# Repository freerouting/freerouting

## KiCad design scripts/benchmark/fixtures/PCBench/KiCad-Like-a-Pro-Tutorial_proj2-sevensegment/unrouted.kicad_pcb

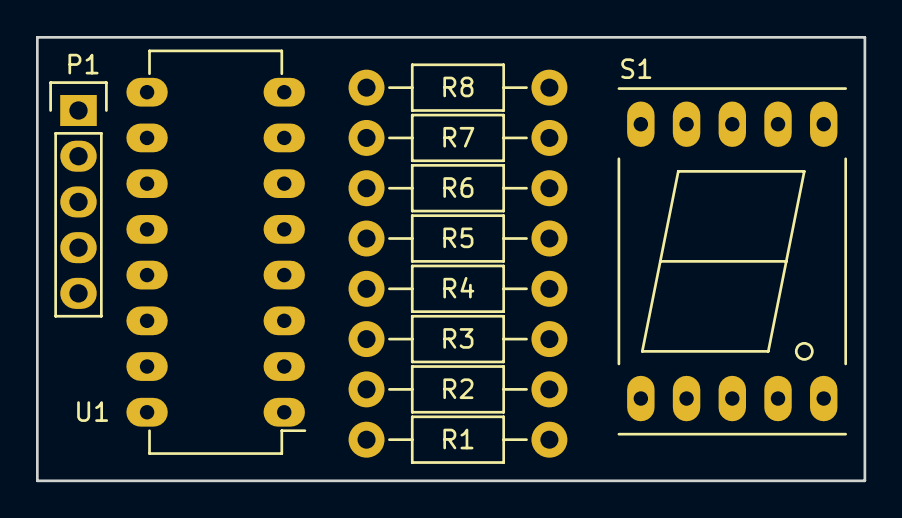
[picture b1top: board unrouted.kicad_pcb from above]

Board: 2 copper layers, 46.0 x 24.6 mm, 11 parts (0 on the bottom side), 21 nets, no tracks yet.

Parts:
P1: CONN_01X05; Pin_Header_Straight_1x05
R1, R2, R3, R4, R5, R6, R7, R8: 220; Resistor_Horizontal_RM10mm
S1: 7SEGM; 7SegmentLED_LTS6760_LTS6780
U1: 74HC595; DIP-16_W7.62mm_LongPads

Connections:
/A: R1.1, S1.7
/B: R2.1, S1.6
/C: R3.1, S1.4
/CLOCK: P1.4, U1.12
/D: R4.1, S1.2
/DATA: P1.3, U1.11
/E: R5.1, S1.1
/F: R6.1, S1.9
/G: R7.1, S1.10
/H: R8.1, S1.5
/LATCH: P1.2, U1.14
/QA: R1.2, U1.15
/QB: R2.2, U1.1
/QC: R3.2, U1.2
/QD: R4.2, U1.3
/QE: R5.2, U1.4
/QF: R6.2, U1.5
/QG: R7.2, U1.6
/QH: R8.2, U1.7
GND: P1.5, U1.8, U1.13
VCC: P1.1, S1.3, S1.8, U1.10, U1.16

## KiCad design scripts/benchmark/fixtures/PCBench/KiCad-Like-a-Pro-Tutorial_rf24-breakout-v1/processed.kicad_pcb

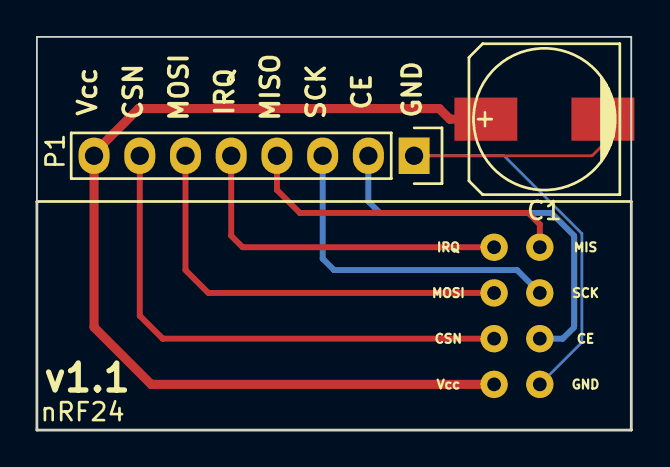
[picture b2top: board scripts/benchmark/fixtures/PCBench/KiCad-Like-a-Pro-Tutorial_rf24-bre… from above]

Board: 2 copper layers, 33.0 x 21.8 mm, 3 parts (0 on the bottom side), 8 nets.

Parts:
C1: 1uF; c_elec_8x10.5
P1: CONN_01X08; Pin_Header_Straight_1x08
U1: nRF24

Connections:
/CE: P1.2, U1.1
/CSN: P1.7, U1.6
/IRQ: P1.5, U1.4
/MIS: P1.4, U1.3
/MOSI: P1.6, U1.5
/SCK: P1.3, U1.2
/Vcc: C1.1, P1.8, U1.7
GND: C1.2, P1.1, U1.0

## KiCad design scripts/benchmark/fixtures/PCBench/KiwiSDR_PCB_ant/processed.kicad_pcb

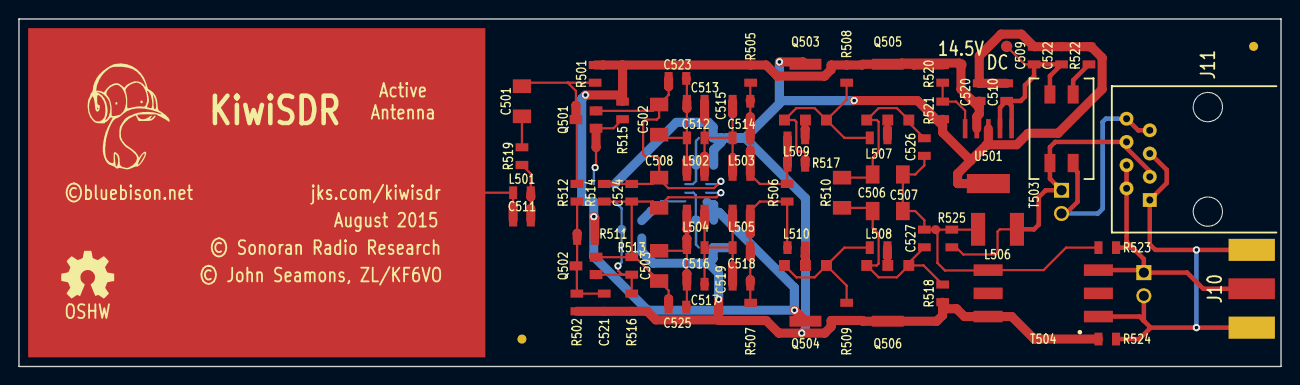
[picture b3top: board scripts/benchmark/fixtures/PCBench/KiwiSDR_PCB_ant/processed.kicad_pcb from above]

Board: 2 copper layers, 138.0 x 38.0 mm, 85 parts (0 on the bottom side), 36 nets.

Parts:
C501, C502, C503, C506, C507, C508: 470n/100; kiwi-SM1206
C504, C505: DNL 470n/100; kiwi-SM1206
C509: 100n/100; kiwi-SM0805
C510, C520: 10u/25; kiwi-SM0805
C511, C512, C513, C514, C515, C516, C517, C518, C519: DNL; kiwi-SM0805
C521: DNL 100n/100; kiwi-SM0805
C522, C523, C524, C525, C526, C527: 1n/100; kiwi-SM0805
EP501: E_FIELD_PROBE; kiwi-E_FIELD_PROBE
FID1, FID2: FIDUCIAL; kiwi-FIDUCIAL_2_SIDE
GFX1: LOGO; kiwi-KIWI_10MM
GFX3: OSHW; kiwi-OSHW_6MM
J10: DNL BNC; kiwi-BNC_SMA_NO_VIP
J11: DNL RJ45; kiwi-RJ45_8
J12: DNL TB_2; kiwi-TB_2P_2_54MM
J13: TB_2; kiwi-TB_2P_2_54MM
L501, L502, L503, L504, L505: 0R; kiwi-SM0805
L506: 100uH; kiwi-SM1812
L507, L508, L509, L510: FB 80Z; kiwi-SM0805
Q501: J310; kiwi-SOT23_DGS
Q502: J271; kiwi-SOT23_DGS
Q503, Q506: BFG31; kiwi-SOT223_EBEC
Q504, Q505: BFG35; kiwi-SOT223_EBEC
Q507: DNL J310; kiwi-SOT23_DGS
R501, R502: 1M; kiwi-SM0805
R503, R504: DNL 100R; kiwi-SM0805
R505, R507: 100K; kiwi-SM0805
R506: 2K2; kiwi-SM0805
R508, R509: 470R; kiwi-SM0805
R510: 10R/0.66W; kiwi-SM1206
R511: DNL 1M; kiwi-SM0805
R512, R515, R516, R519, R523, R524: 0R; kiwi-SM0805
R513, R518: DNL 0R; kiwi-SM0805
R514: 100R; kiwi-SM0805
R517: DNL 47R; kiwi-SM0805
R520: 11K; kiwi-SM0805
R521: 1K; kiwi-SM0805
R522: DNL; kiwi-SM0805
R525: 1K5; kiwi-SM0805
T501: DNL T-622; kiwi-MCL_KK81
T502, T504: DNL T1-6; kiwi-MCL_KK81
T503: CMC 2 mH; kiwi-CMC
TP501, TP502: TEST_POINT; kiwi-TP_1250
U501: TPS7A4501; kiwi-SOT223_6

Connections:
/14.55: C520.1, Q504.C, Q505.C, R501.1, R503.1, R505.1, R508.1, R511.1, R515.1, R520.1, T501.3, T502.4, TP502.1, U501.4
/ANT2: C511.2, L501.1, R519.1
/ANT3: C501.1, R519.2
/ANT4: C501.2, Q501.G, R501.2, R512.1
/B1H: L509.2, Q503.B
/B1L: L510.2, Q504.B
/B2H: L507.2, Q505.B
/B2L: L508.2, Q506.B
/BIAS: C521.1, Q502.G, R502.2, R511.2, R512.2
/BIAS+: J11.3, J11.6, J12.1, L506.2, R525.1, T503.3
/BIAS-: J11.7, J11.8, J12.2, T503.4
/DCIN: C509.1, C510.1, C522.1, T503.2, TP501.1, U501.1, U501.2
/E1H: L507.1, Q503.E1, Q503.E2, R508.2, R517.1
/E1L: L508.1, Q504.E1, Q504.E2, R509.1
/E2H: C506.1, C526.1, Q505.E1, Q505.E2, R510.1
/E2L: C507.1, C527.1, Q506.E1, Q506.E2, R510.2, R518.1
/EPROBE: C511.1, EP501.1, L501.2
/FB1: Q501.D, R515.2, T502.6
/FB2: Q502.D, Q507.G, R513.1, R516.2, T502.3
/FB3: Q507.D, T501.4
/JHI: C502.1, C508.1, C523.1, C524.1, Q501.S, R514.2, T501.1
/JLO: C503.1, C508.2, C524.2, C525.1, Q502.S, R513.2, R514.1, T501.2
/NF1H: C502.2, C512.1, C513.1, C523.2, L502.1
/NF1L: C503.2, C516.1, C517.1, C525.2, L504.1
/NF2H: C512.2, C513.2, C514.1, C515.1, L502.2, L503.1
/NF2L: C516.2, C517.2, C518.1, C519.1, L504.2, L505.1
/NF3H: C514.2, C515.2, L503.2, L509.1, R505.2, R506.1, R517.2
/NF3L: C518.2, C519.2, L505.2, L510.1, R506.2, R507.1
/OUT: C506.2, C507.2, C526.2, C527.2, L506.1, R523.2, R525.2, T504.3
/RX+: J10.1, J11.2, J11.4, J13.1, R523.1, T504.4
/RX-: J10.2, J10.3, J11.1, J11.5, J13.2, R524.1, T504.6
/THI: C505.1, R504.2, T501.6
/TLO: C504.2, R503.2, T501.5
/TP: R522.1, T503.1
/VADJ: R520.2, R521.2, U501.5
GND: C504.1, C505.2, C509.2, C510.2, C520.2, C521.2, C522.2, Q503.C, Q506.C, Q507.S, R502.1, R504.1, R507.2, R509.2, R516.1, R518.2, R521.1, R522.2, R524.2, T502.1, T504.1, U501.3, U501.TAB

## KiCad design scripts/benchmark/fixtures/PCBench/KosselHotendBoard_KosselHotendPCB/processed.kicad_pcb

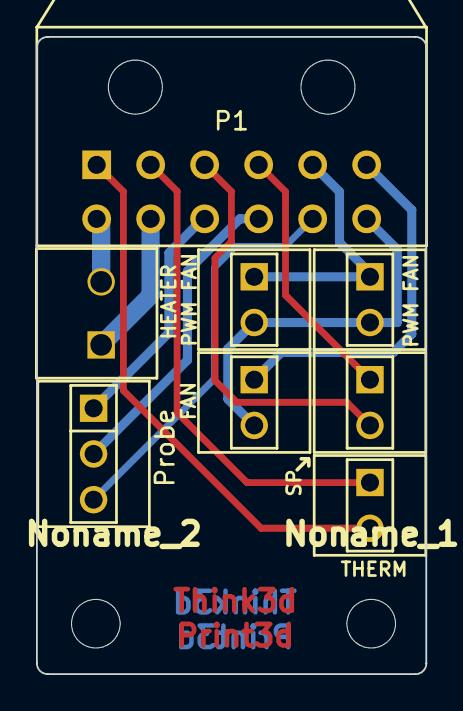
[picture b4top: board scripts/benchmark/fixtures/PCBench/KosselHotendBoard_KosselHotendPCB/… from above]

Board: 2 copper layers, 21.6 x 35.4 mm, 10 parts (0 on the bottom side), 12 nets.

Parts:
Noname_1, Noname_2: Fixing_2.7mm
P1: CONN_6X2; PIN_ARRAY_6x2_lugs
P2: HEATER; 3.5MM_2X1
P3: THERM; PIN_ARRAY_2X1_KK
P4, P7: PWM FAN; PIN_ARRAY_2X1_KK
P5: FAN; PIN_ARRAY_2X1_KK
P6: Probe; PIN_ARRAY_3X1_KK
P8: SP; PIN_ARRAY_2X1_KK

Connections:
+12V: P1.2, P2.2
FAN +: P1.12, P4.2, P5.2, P7.2
GND: P1.11, P5.1
Heater -VE: P1.4, P2.1
PWM Fan -VE: P1.9, P4.1, P7.1
Probe GND: P1.8, P6.2
Probe Sig: P1.10, P6.3
Spare1: P1.7, P8.1
Spare2: P1.5, P8.2
Therm1: P1.3, P3.1
Therm2: P1.1, P3.2
Vcc: P1.6, P6.1

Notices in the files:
scripts/benchmark/fixtures/PCBench/KiwiSDR_PCB_ant/processed.kicad_pcb:
© John Seamons, ZL/KF6VO
© Sonoran Radio Research
©bluebison.net
scripts/benchmark/fixtures/PCBench/KosselHotendBoard_KosselHotendPCB/processed.kicad_pcb:
(c) Licensed under the CERN OHL V1.2
CERN OHL 1.2
